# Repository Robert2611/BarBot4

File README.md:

# BarBot4

BarBot4 is a high-end, automated cocktail-mixing machine designed for precision and ease of use. It combines a Raspberry Pi-powered touch interface with modular microcontroller-based hardware to deliver perfectly mixed drinks every time.

## ✨ Features

- **Automated Mixing**: Precise control over ingredient dispensing and sequence.
- **Modular Design**: Support for peripheral modules like mixers, crushers, and straw dispensers.
- **Smart Scale Integration**: Real-time weight tracking for accurate pours.
- **Touchscreen GUI**: Modern, user-friendly interface built with PyQt5.
- **Customizable Recipes**: Easily create and manage your own cocktail database.
- **Wireless Communication**: Bluetooth-based control between the Pi and hardware sub-modules.

## 🛠️ Hardware Requirements

To build a BarBot4, you will need:
- **Main Controller**: Raspberry Pi (Bookworm or Trixie recommended) with a touchscreen.
- **Mainboard**: ESP32-based controller for motor and pump management.
- **Balance Board (Mandatory)**: An Atmega328p-based module for accurate weight sensing.
    - **Sensor**: HX711 Load Cell amplifier for weight measurement.
- **Optional Sub-modules**: AVR (Arduino) based modules for specific functions (e.g., Ice Crusher, Mixer, Straw Dispenser).
- **Firmware**: Pre-compiled binaries for all modules are available in the [GitHub Releases](https://github.com/Robert2611/BarBot4/releases).

## 🚀 Quick Start

### 1. Firmware Installation
For ease of setup, pre-compiled firmware binaries are automatically generated and attached to each [GitHub Release](https://github.com/Robert2611/BarBot4/releases).

1. Download the `firmware.zip` from the latest release.
2. Extract the archive on a Windows PC.
3. Run `flash.bat` and follow the on-screen instructions to flash your Mainboard (ESP32) or sub-modules (Atmega328p).
   - *Note: Flashing scripts for Linux/macOS users can be found in the `/firmware` directory.*

### 2. Pi Software Installation
The easiest way to set up the BarBot software on a fresh Raspberry Pi OS is to use the automated install script:

```bash
curl -sSL https://raw.githubusercontent.com/Robert2611/BarBot4/master/raspberry/install.sh | bash
```

This script handles dependencies, virtual environment setup, and system configuration. **It also configures the application to start automatically on boot**, so there is no need to run it manually after the initial setup.

## 🛠️ Development

If you are developing for BarBot4 or need to run it manually for testing, you can use the following commands:

### Running BarBot Manually
- `barbot`: Start the standard interface.
- `barbot-demo`: Start in demo mode (uses mockup hardware for testing).
- `barbot-with-log`: Start with console logging enabled.

### Local Installation
To install the package in editable mode from the repository:
```bash
cd raspberry
pip install -e .
```

## 📂 Project Structure

The project is organized to separate physical design, electronics, and software:
- `/CAD`: 3D models for the chassis and components.
- `/elektronik`: PCB designs and schematics.
- `/firmware`: Microcontroller source code (C++/PlatformIO).
- `/raspberry`: Main Python application logic and GUI.

For a detailed breakdown of all directories, please refer to [README_STRUCTURE.md](./README_STRUCTURE.md).

## 🤝 Contributing

Contributions are welcome! Whether it's a new recipe, a bug fix, or a feature request, feel free to open an issue or submit a pull request.

## 📜 License
[MIT](https://choosealicense.com/licenses/mit/)

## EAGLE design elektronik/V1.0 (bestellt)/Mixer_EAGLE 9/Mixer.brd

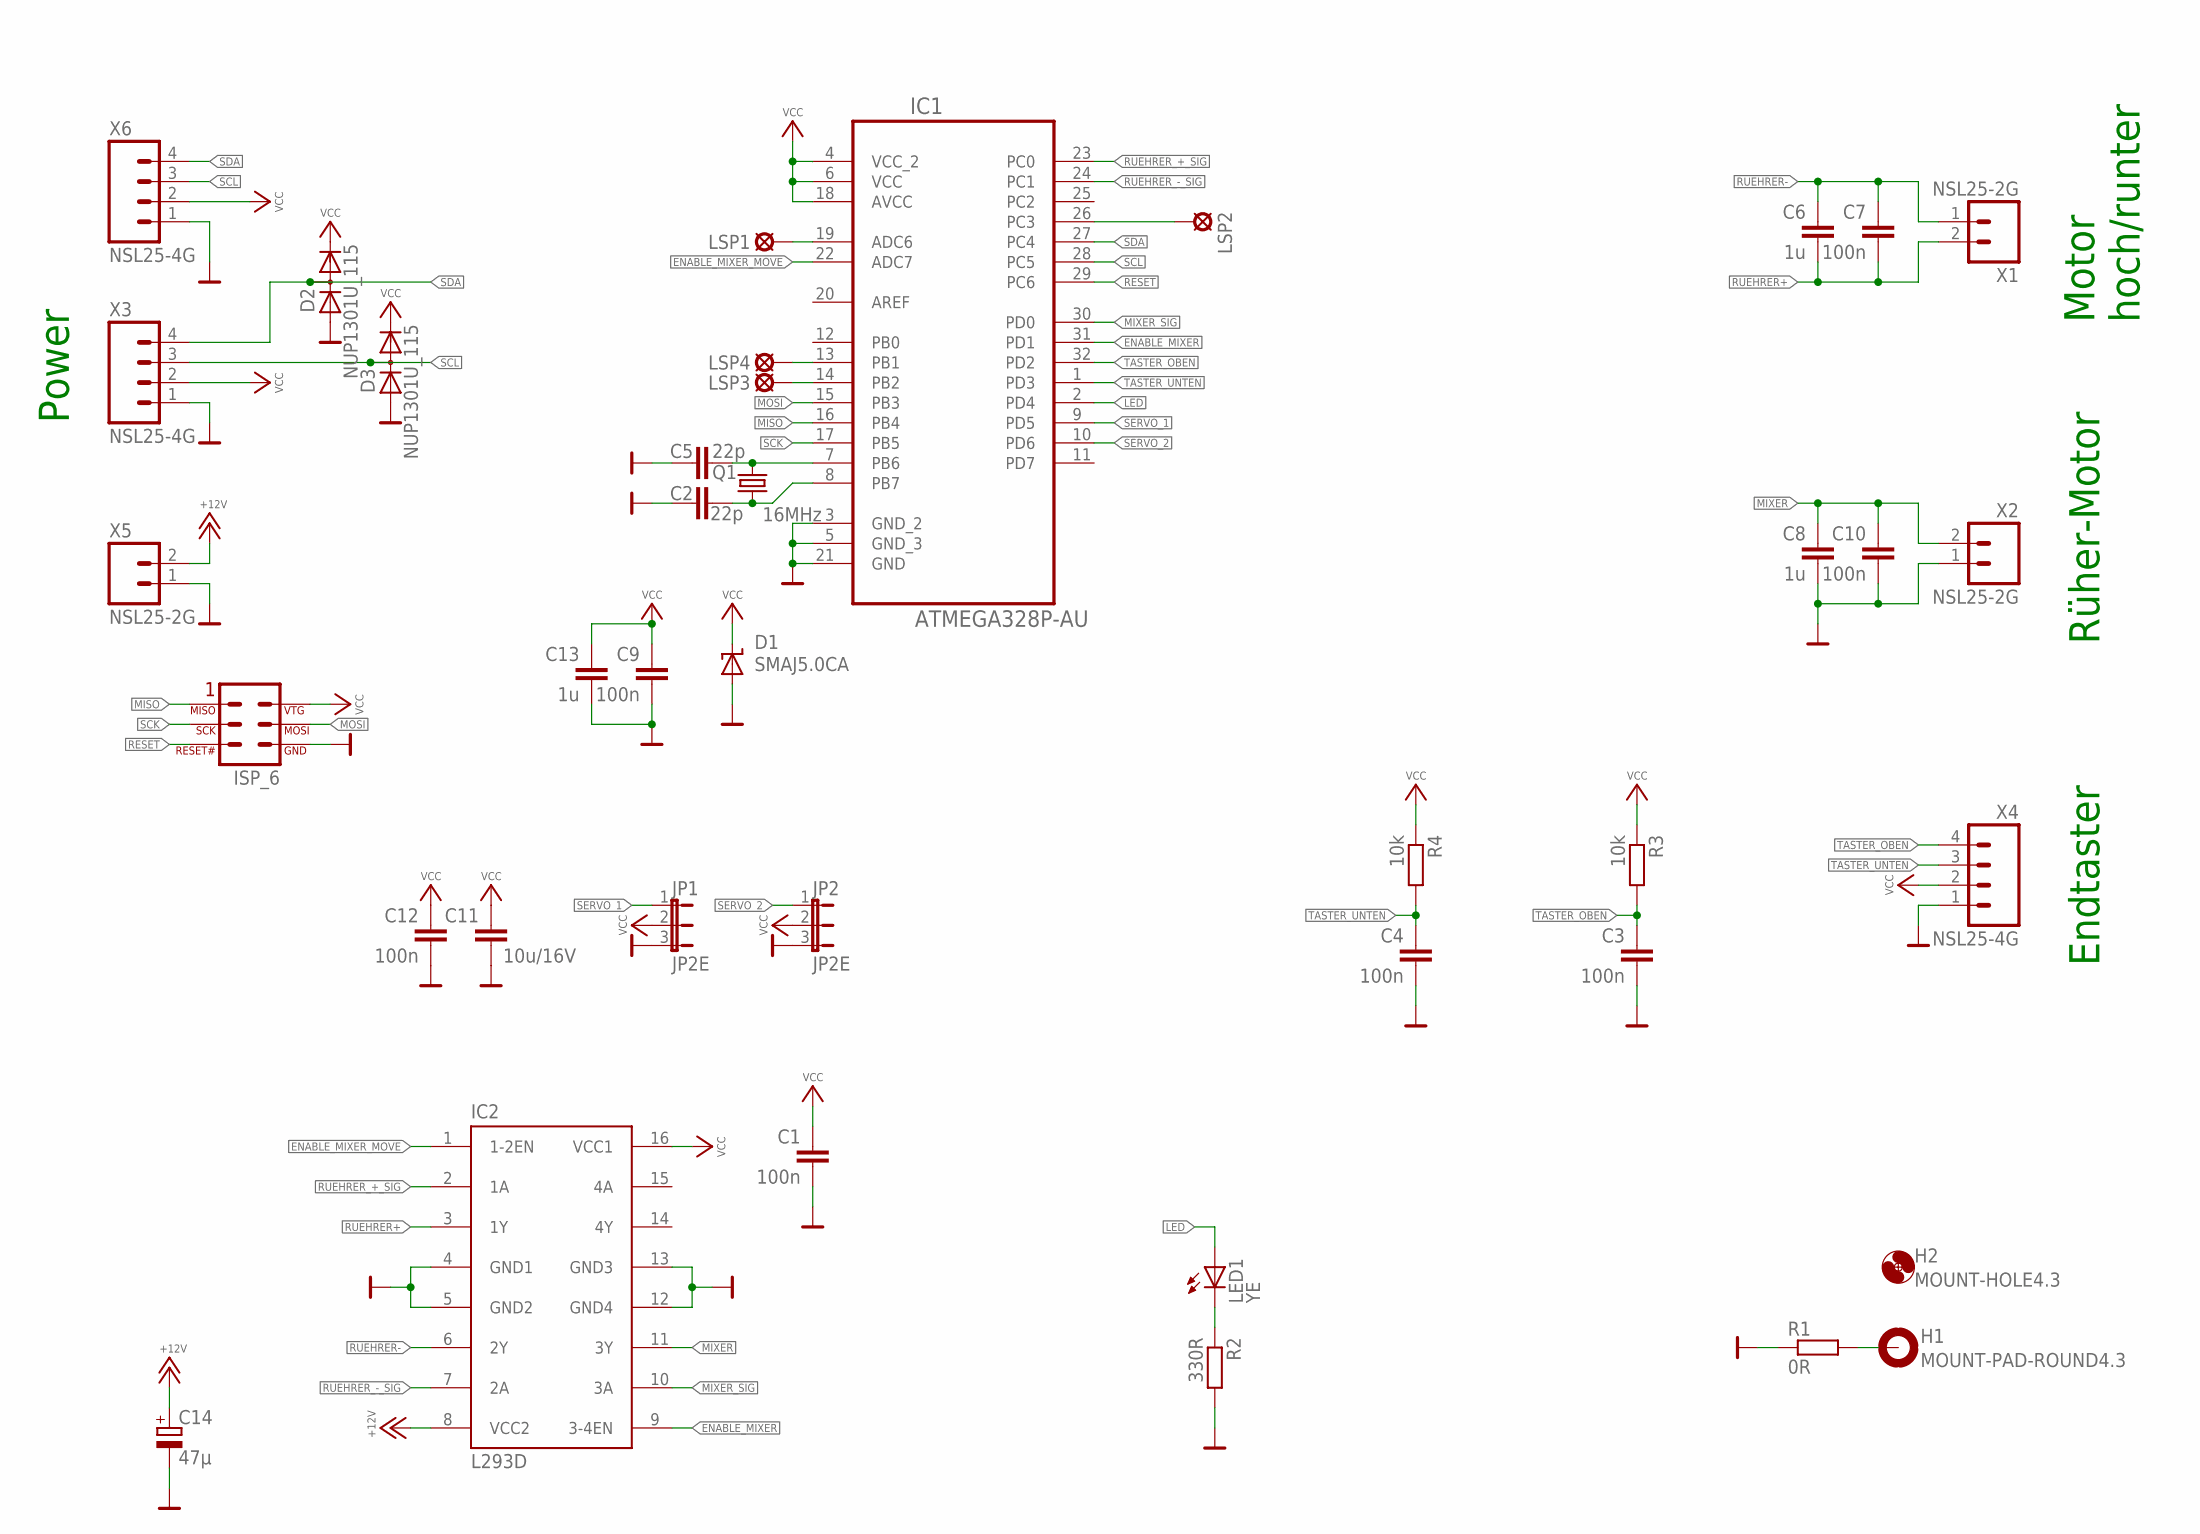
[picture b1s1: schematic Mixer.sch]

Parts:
C1, C3, C4, C7, C9, C10, C12: 100n; 0805CRH
C2, C5: 22p; 0805CRH
C6, C8, C13: 1u; 0805CRH
C11: 10u/16V; 0805CRH
C14: 47µ; 153CLV-0405
D1: SMAJ5.0CA; SMA-DO214AC
D2, D3: NUP1301U_115; SOT323-3
H1: MOUNT-PAD-ROUND4.3; 4,3-PAD
H2: MOUNT-HOLE4.3; 4,3
IC1: ATMEGA328P-AU; QFP80P900X900X120-32N
IC2: L293D; DIL16
JP1, JP2: JP2E; JP2
LED1: YE; CHIPLED_0805
LSP1, LSP2, LSP3, LSP4: LSP06
Q1: 16MHz; HC49UP
R1: 0R; 0805CRH
R2: 330R; 0805CRH
R3, R4: 10k; 0805CRH
SV1: ATMEL_ISP_6; ML6
X1, X2, X5: NSL25-2G
X3, X4, X6: NSL25-4G

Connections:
+12V: C14.+, IC2.8 (VCC2), X5.2
ADC6: IC1.19 (ADC6), LSP1.MP
ENABLE_MIXER: IC1.31 (PD1), IC2.9 (3-4EN)
ENABLE_MIXER_MOVE: IC1.22 (ADC7), IC2.1 (1-2EN)
GND: C1.2, C2.1, C3.2, C4.2, C5.1, C8.2, C9.2, C10.2, C11.2, C12.2, C13.2, C14.-, D1.A, D2.1, D3.1, IC1.3 (GND_2), IC1.5 (GND_3), IC1.21 (GND), IC2.4 (GND1), IC2.5 (GND2), IC2.12 (GND4), IC2.13 (GND3), JP1.3, JP2.3, R1.1, R2.2, SV1.6, X2.1, X3.1, X4.1, X5.1, X6.1
LED: IC1.2 (PD4), LED1.A
MISO: IC1.16 (PB4), SV1.1
MIXER: C8.1, C10.1, IC2.11 (3Y), X2.2
MIXER_SIG: IC1.30 (PD0), IC2.10 (3A)
MOSI: IC1.15 (PB3), SV1.4
unnamed: H1.B4,3, R1.2
unnamed: LED1.C, R2.1
unnamed: IC1.26 (PC3), LSP2.MP
unnamed: C5.2, IC1.7 (PB6), Q1.2
unnamed: C2.2, IC1.8 (PB7), Q1.1
unnamed: IC1.14 (PB2), LSP3.MP
unnamed: IC1.13 (PB1), LSP4.MP
RESET: IC1.29 (PC6), SV1.5
RUEHRER+: C6.2, C7.2, IC2.3 (1Y), X1.2
RUEHRER-: C6.1, C7.1, IC2.6 (2Y), X1.1
RUEHRER_+_SIG: IC1.23 (PC0), IC2.2 (1A)
RUEHRER_-_SIG: IC1.24 (PC1), IC2.7 (2A)
SCK: IC1.17 (PB5), SV1.3
SCL: D3.3, IC1.28 (PC5), X3.3, X6.3
SDA: D2.3, IC1.27 (PC4), X3.4, X6.4
SERVO_1: IC1.9 (PD5), JP1.1
SERVO_2: IC1.10 (PD6), JP2.1
TASTER_OBEN: C3.1, IC1.32 (PD2), R3.2, X4.4
TASTER_UNTEN: C4.1, IC1.1 (PD3), R4.2, X4.3
VCC: C1.1, C9.1, C11.1, C12.1, C13.1, D1.K (C), D2.2, D3.2, IC1.4 (VCC_2), IC1.6 (VCC), IC1.18 (AVCC), IC2.16 (VCC1), JP1.2, JP2.2, R3.1, R4.1, SV1.2, X3.2, X4.2, X6.2

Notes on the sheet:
Power
Rüher-Motor
Endtaster
Motor hoch/runter

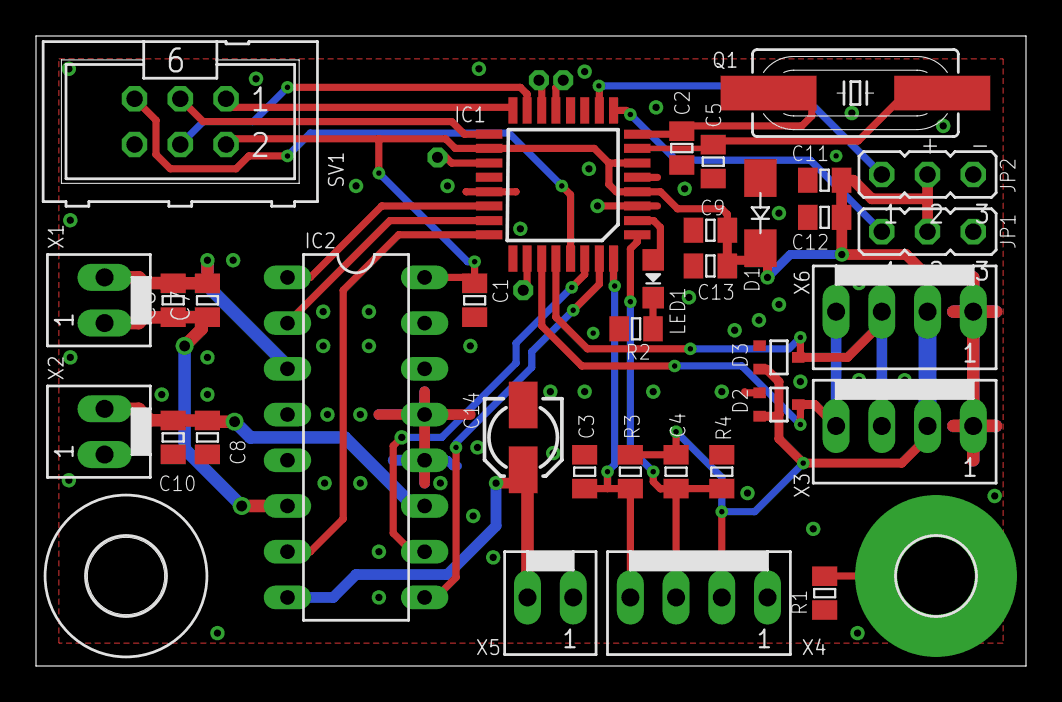
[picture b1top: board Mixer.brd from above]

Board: 2 copper layers, 55.0 x 35.0 mm, 40 parts (0 on the bottom side), 30 nets.

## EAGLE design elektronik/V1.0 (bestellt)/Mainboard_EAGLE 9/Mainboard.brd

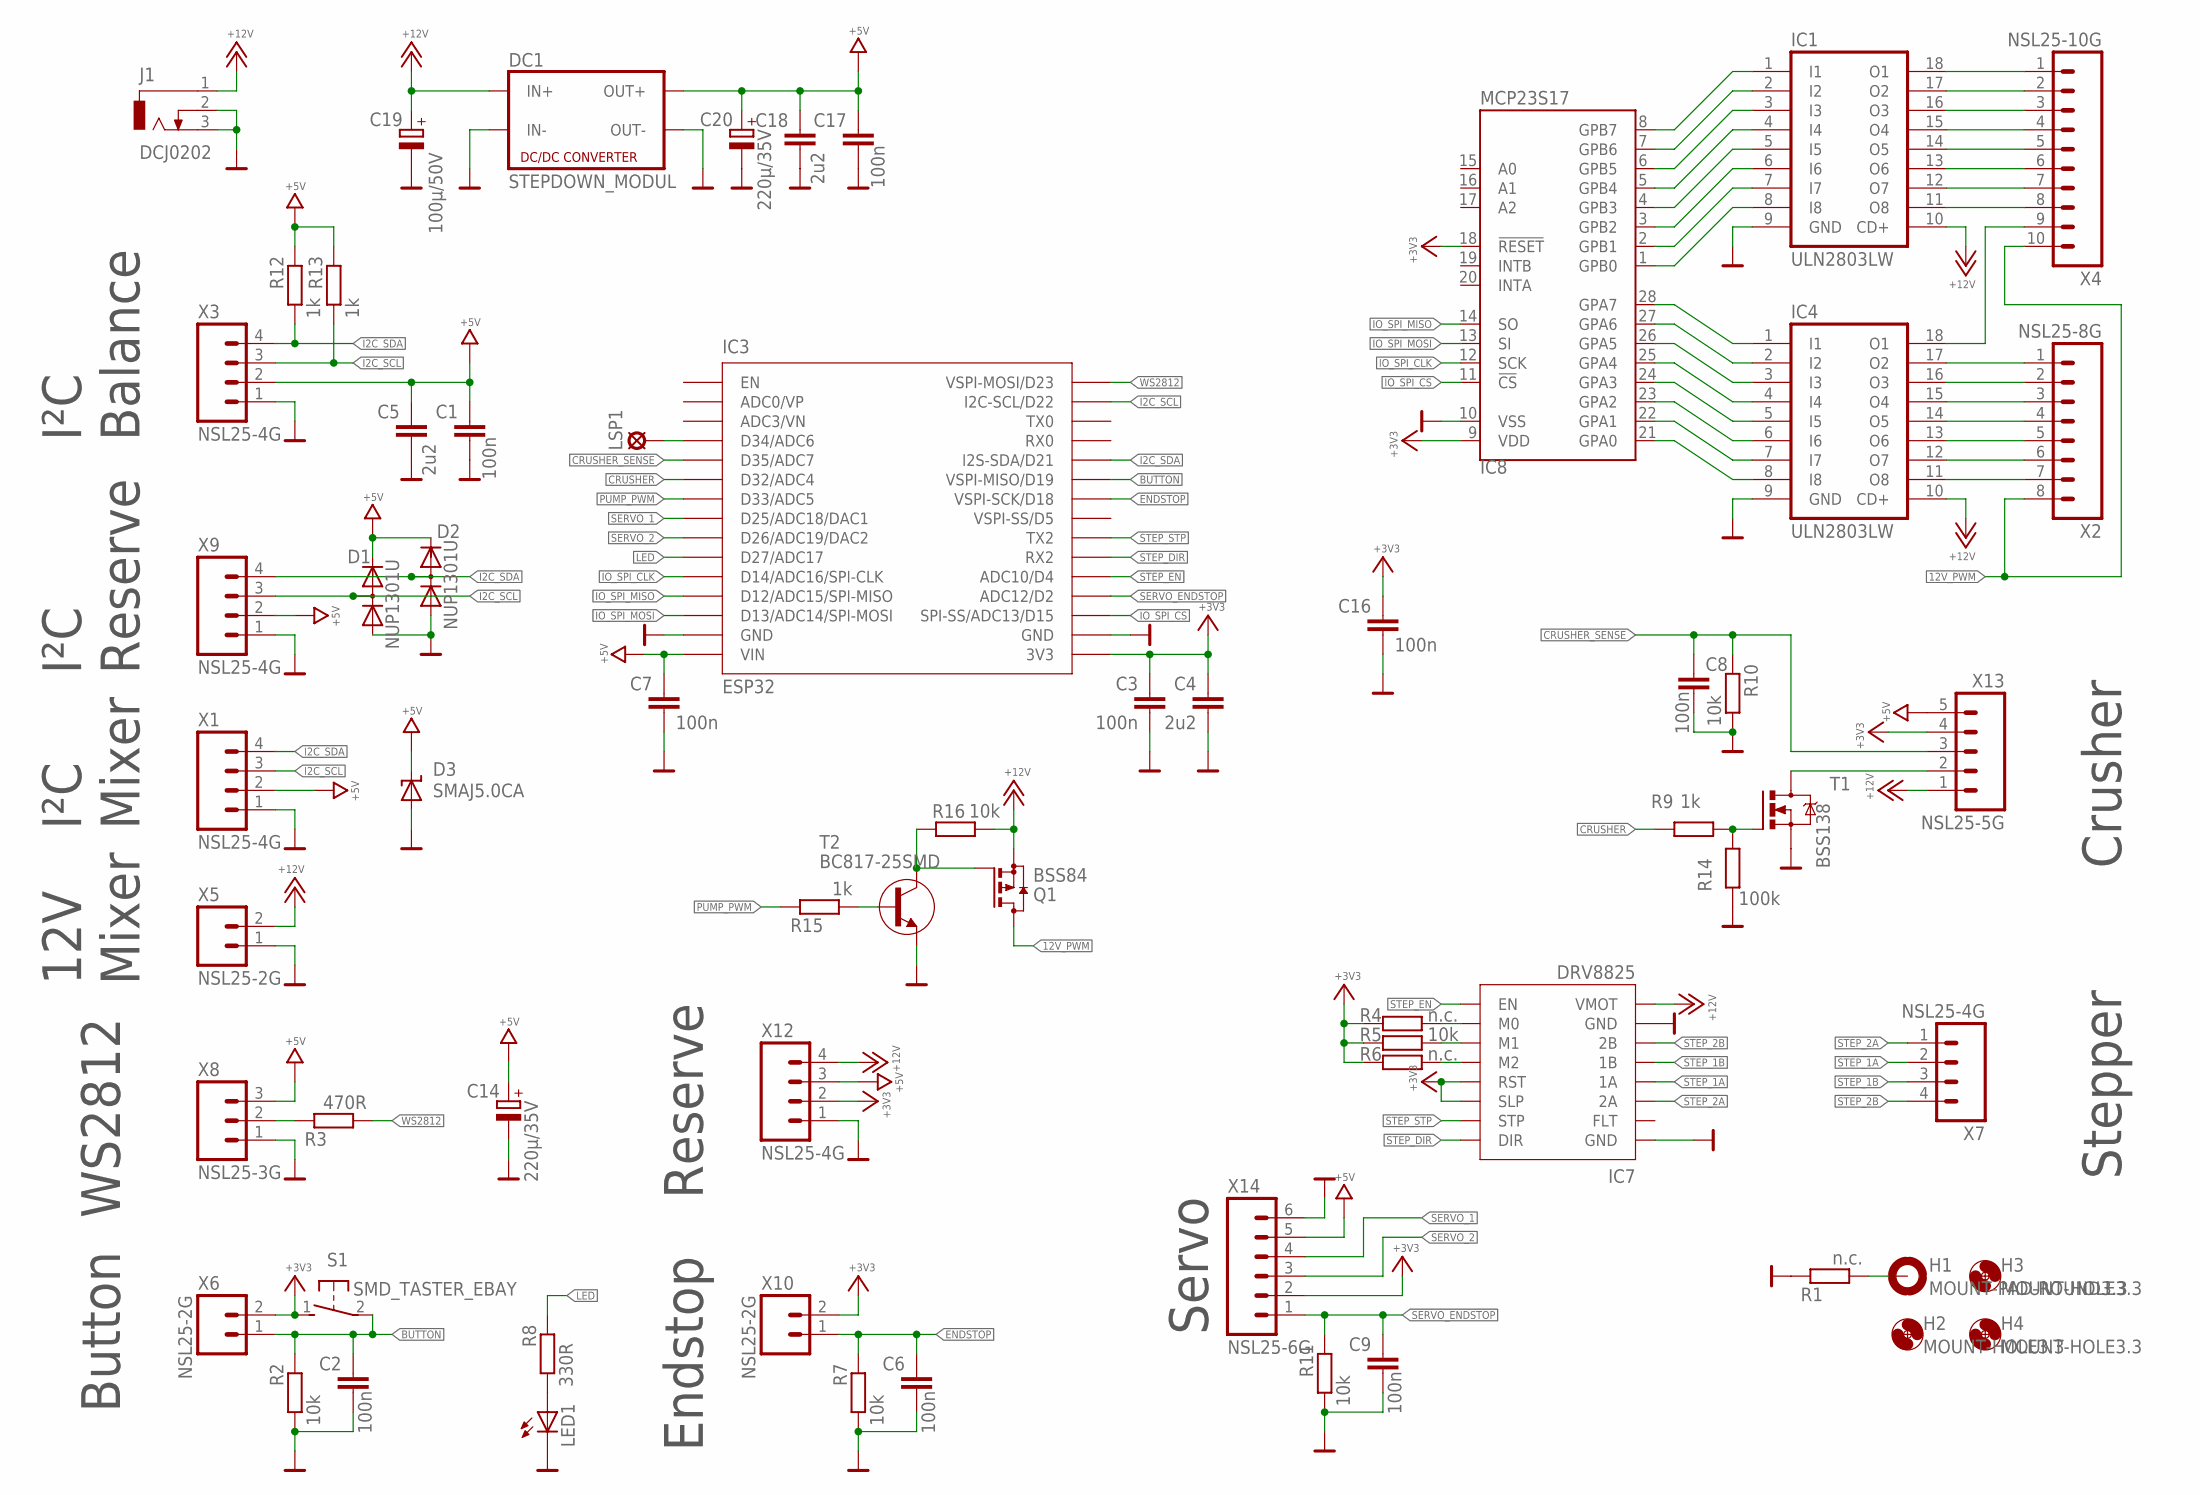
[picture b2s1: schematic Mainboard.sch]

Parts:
C1, C2, C3, C6, C7, C8, C9, C16, C17: 100n; 0805CRH
C4, C5, C18: 2u2; 0805CRH
C14, C20: 220µ/35V; 153CLV-1010
C19: 100µ/50V; 153CLV-1010
D1, D2: NUP1301U; SOT323-3
D3: SMAJ5.0CA; SMA-DO214AC
DC1: STEPDOWN_MODUL
H1: MOUNT-PAD-ROUND3.3; 3,3-PAD
H2, H3, H4: MOUNT-HOLE3.3; 3,3
IC1, IC4: ULN2803LW; SO18W
IC3: ESP32
IC7: DRV8825
IC8: MCP23S17; SOIC-28
J1: DCJ0202
LED1: LEDCHIPLED_0805; CHIPLED_0805
LSP1: LSP06
Q1: BSS84; SOT23
R1, R4, R6: n.c.; 0805CRH
R2, R5, R7, R10, R11, R16: 10k; 0805CRH
R3: 470R; 0805CRH
R8: 330R; 0805CRH
R9, R12, R13, R15: 1k; 0805CRH
R14: 100k; 0805CRH
S1: SMD_TASTER_EBAY; DTSM3XN
T1: BSS138; SOT23
T2: BC817-25SMD; SOT23-BEC
X1, X3, X7, X9, X12: NSL25-4G
X2: NSL25-8G
X4: NSL25-10G
X5, X6, X10: NSL25-2G
X8: NSL25-3G
X13: NSL25-5G
X14: NSL25-6G

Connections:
12V_PWM: Q1.3 (D), X2.8, X4.10
+3V3: C3.1, C4.1, C16.1, IC3.3V3, IC7.RST, IC7.SLP, IC8.9 (VDD), IC8.18 (!RESET!), R4.1, R5.1, R6.1, S1.1 (S), X6.2, X10.2, X12.2, X13.4, X14.2
+5V: C1.1, C5.1, C7.1, C14.+, C17.1, C18.1, C20.+, D1.2, D2.2, D3.K (C), DC1.OUT+, IC3.VIN, R12.1, R13.1, X1.2, X3.2, X8.3, X9.2, X12.3, X13.5, X14.5
+12V: C19.+, DC1.IN+, IC1.10 (CD+), IC4.10 (CD+), IC7.VMOT, J1.1, Q1.2 (S), R16.2, X5.2, X12.4, X13.1
ADC3/VN: IC3.VN (ADC3/VN)
BUTTON: C2.1, IC3.D19 (VSPI-MISO/D19), R2.1, S1.2, X6.1
CRUSHER: IC3.D32 (D32/ADC4), R9.1
CRUSHER_SENSE: C8.1, IC3.D35 (D35/ADC7), R10.1, X13.3
ENDSTOP: C6.1, IC3.D18 (VSPI-SCK/D18), R7.1, X10.1
GND: C1.2, C2.2, C3.2, C4.2, C5.2, C6.2, C7.2, C8.2, C9.2, C14.-, C16.2, C17.2, C18.2, C19.-, C20.-, D1.1, D2.1, D3.A, DC1.IN-, DC1.OUT-, IC1.9 (GND), IC3.GND@1 (GND), IC3.GND@2 (GND), IC4.9 (GND), IC7.GND@1 (GND), IC7.GND@2 (GND), IC8.10 (VSS), J1.2, J1.3, LED1.C, R1.1, R2.2, R7.2, R10.2, R11.2, R14.1, T1.2 (S), T2.E, X1.1, X3.1, X5.1, X8.1, X9.1, X12.1, X14.6
I2C_SCL: D1.3, IC3.D22 (I2C-SCL/D22), R13.2, X1.3, X3.3, X9.3
I2C_SDA: D2.3, IC3.D21 (I2S-SDA/D21), R12.2, X1.4, X3.4, X9.4
IO_SPI_CLK: IC3.D14 (D14/ADC16/SPI-CLK), IC8.12 (SCK)
IO_SPI_CS: IC3.D15 (SPI-SS/ADC13/D15), IC8.11 (!CS!)
IO_SPI_MISO: IC3.D12 (D12/ADC15/SPI-MISO), IC8.14 (SO)
IO_SPI_MOSI: IC3.D13 (D13/ADC14/SPI-MOSI), IC8.13 (SI)
LED: IC3.D27 (D27/ADC17), R8.1
unnamed: LED1.A, R8.2
unnamed: T1.3 (D), X13.2
unnamed: R9.2, R14.2, T1.1 (G)
unnamed: Q1.1 (G), R16.1, T2.C
unnamed: R15.2, T2.B
unnamed: IC3.D34 (D34/ADC6), LSP1.MP
unnamed: R3.1, X8.2
unnamed: H1.B3,3, R1.2
unnamed: IC4.8 (I8), IC8.21 (GPA0)
unnamed: IC4.7 (I7), IC8.22 (GPA1)
unnamed: IC4.6 (I6), IC8.23 (GPA2)
unnamed: IC4.5 (I5), IC8.24 (GPA3)
unnamed: IC4.4 (I4), IC8.25 (GPA4)
unnamed: IC4.3 (I3), IC8.26 (GPA5)
unnamed: IC4.2 (I2), IC8.27 (GPA6)
unnamed: IC1.18 (O1), X4.1
unnamed: IC1.17 (O2), X4.2
unnamed: IC1.16 (O3), X4.3
unnamed: IC1.15 (O4), X4.4
unnamed: IC1.14 (O5), X4.5
unnamed: IC1.13 (O6), X4.6
unnamed: IC1.12 (O7), X4.7
unnamed: IC1.11 (O8), X4.8
unnamed: IC4.18 (O1), X4.9
unnamed: IC4.17 (O2), X2.1
unnamed: IC4.16 (O3), X2.2
unnamed: IC4.15 (O4), X2.3
unnamed: IC4.14 (O5), X2.4
unnamed: IC4.13 (O6), X2.5
unnamed: IC4.12 (O7), X2.6
unnamed: IC4.11 (O8), X2.7
unnamed: IC4.1 (I1), IC8.28 (GPA7)
unnamed: IC1.8 (I8), IC8.1 (GPB0)
unnamed: IC7.M0, R4.2
unnamed: IC7.M1, R5.2
unnamed: IC7.M2, R6.2
unnamed: IC1.7 (I7), IC8.2 (GPB1)
unnamed: IC1.6 (I6), IC8.3 (GPB2)
unnamed: IC1.5 (I5), IC8.4 (GPB3)
unnamed: IC1.4 (I4), IC8.5 (GPB4)
unnamed: IC1.3 (I3), IC8.6 (GPB5)
unnamed: IC1.2 (I2), IC8.7 (GPB6)
unnamed: IC1.1 (I1), IC8.8 (GPB7)
PUMP_PWM: IC3.D33 (D33/ADC5), R15.1
SERVO_1: IC3.D25 (D25/ADC18/DAC1), X14.4
SERVO_2: IC3.D26 (D26/ADC19/DAC2), X14.3
SERVO_ENDSTOP: C9.1, IC3.D2 (ADC12/D2), R11.1, X14.1
STEP_1A: IC7.1A, X7.2
STEP_1B: IC7.1B, X7.3
STEP_2A: IC7.2A, X7.1
STEP_2B: IC7.2B, X7.4
STEP_DIR: IC3.RX2, IC7.DIR
STEP_EN: IC3.D4 (ADC10/D4), IC7.EN
STEP_STP: IC3.TX2, IC7.STP
WS2812: IC3.D23 (VSPI-MOSI/D23), R3.2

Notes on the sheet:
I²C Balance
I²C Mixer
12V Mixer
WS2812
I²C Reserve
Button
Endstop
Reserve
Stepper
Crusher
Servo

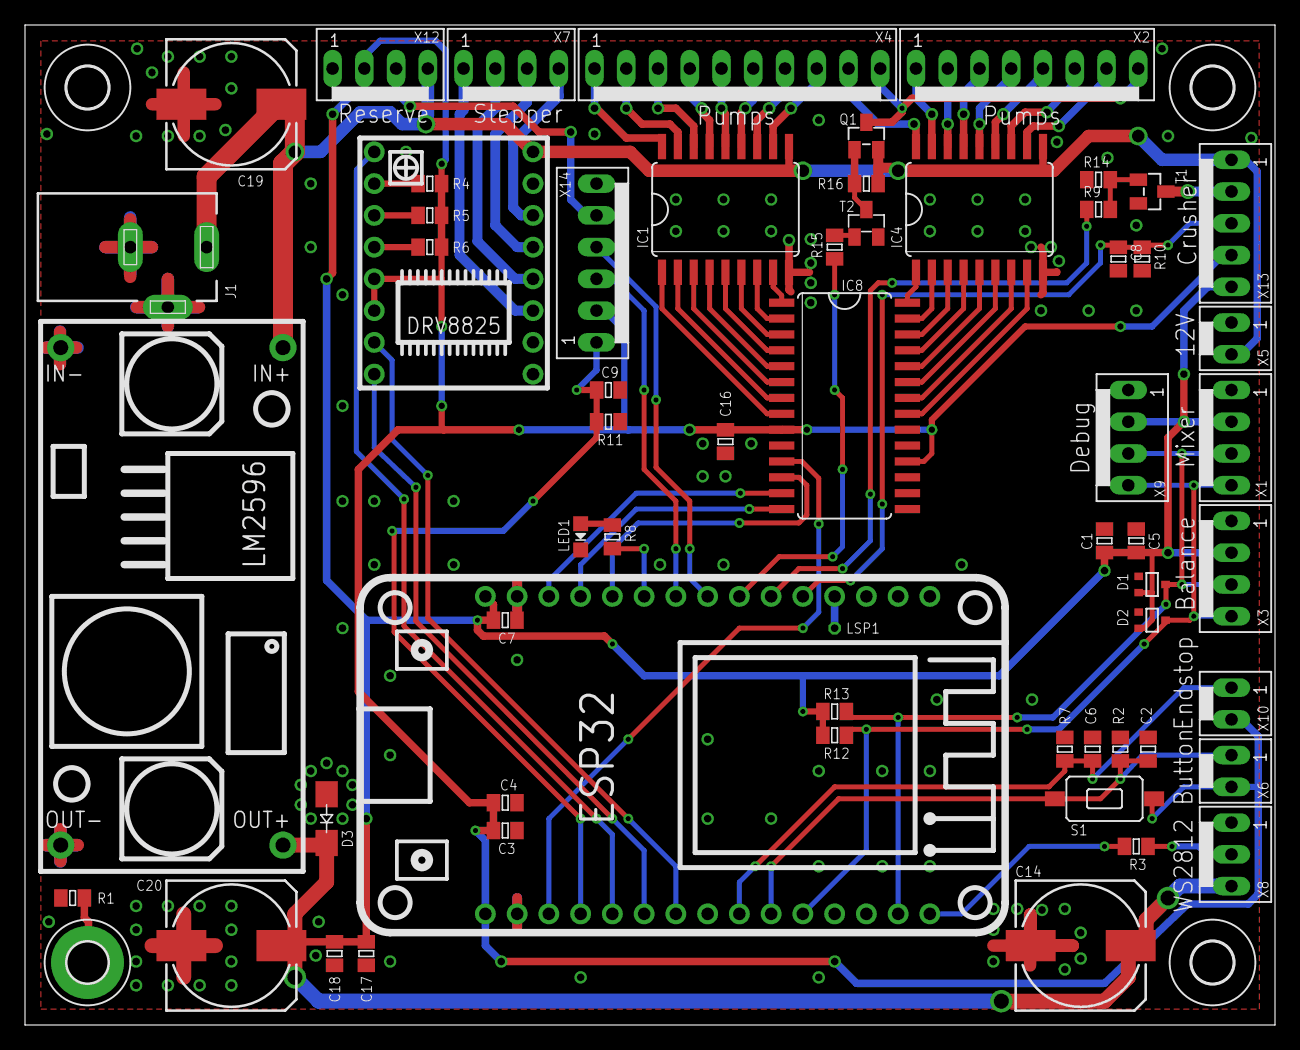
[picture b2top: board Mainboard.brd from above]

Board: 2 copper layers, 100.0 x 80.0 mm, 64 parts (0 on the bottom side), 71 nets.

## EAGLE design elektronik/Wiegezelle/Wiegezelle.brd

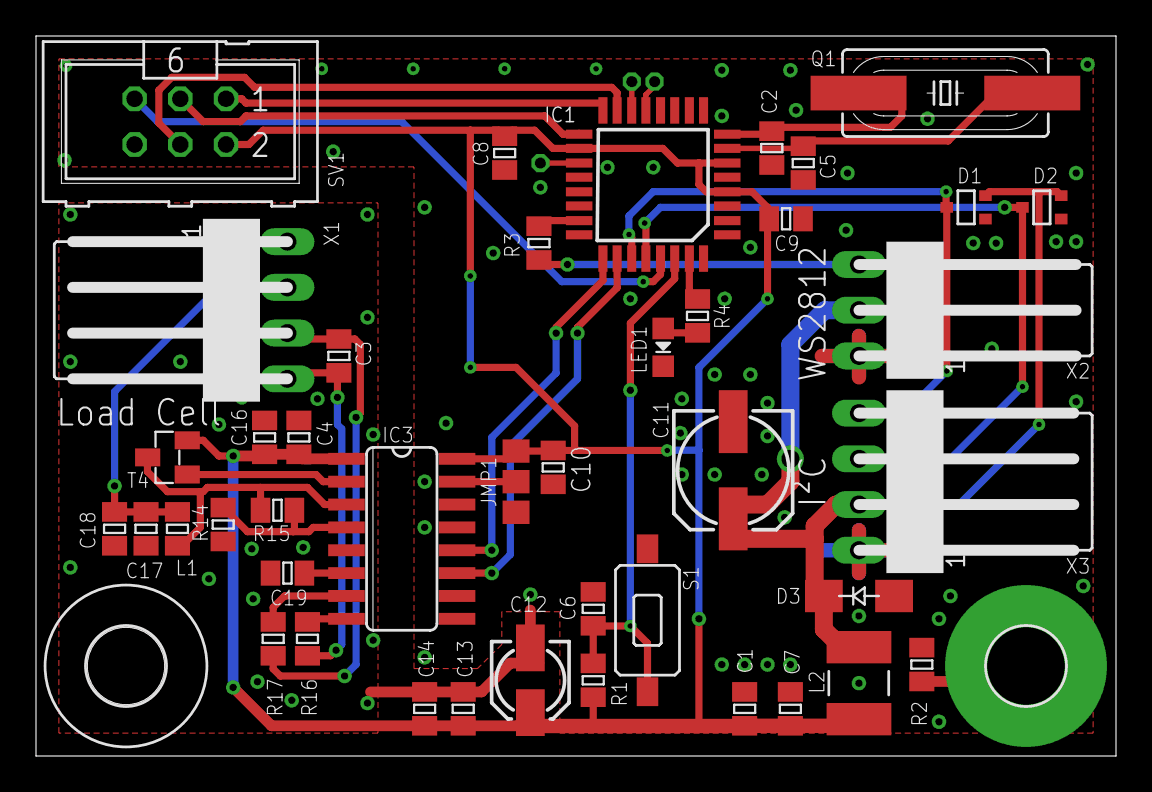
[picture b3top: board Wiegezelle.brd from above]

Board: 2 copper layers, 60.0 x 40.0 mm, 47 parts (0 on the bottom side), 33 nets.

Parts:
C1: 1n; 0805CRH
C2, C5: 22p; 0805CRH
C3, C6, C7, C8, C9, C10, C14, C16, C17, C19: 100n; 0805CRH
C4: 1u; 0805CRH
C11: 100u; 153CLV-0605
C12: 47u; 153CLV-0405
C13: 2u2; 0805CRH
C18: 10u; 0805CRH
D1, D2: NUP1301U_115; SOT323-3
D3: SMAJ5.0CA; SMA-DO214AC
H1: MOUNT-PAD-ROUND4.3; 4,3-PAD
H2: MOUNT-HOLE4.3; 4,3
IC1: ATMEGA328P-AU; QFP80P900X900X120-32N
IC3: HX711; SO16
JMP1: 0R-JUMPA; A0R-JMP
L1: 3u3; 0805CRH
L2: 22u; L4532P
LED1: YE; CHIPLED_0805
LSP1, LSP2, LSP3: LSP06
Q1: 16MHz; HC49UP
R1: 10k; 0805CRH
R2: 0R; 0805CRH
R3: 470R; 0805CRH
R4: 220R; 0805CRH
R14: 1k; 0805CRH
R15: 2k2; 0805CRH
R16, R17: 100R; 0805CRH
S1: SMD_TASTER_EBAY; DTSM3XN
SV1: ATMEL_ISP_6; ML6
T4: BC807-16SMD; SOT23-BEC
X1, X3: NSL25-4W
X2: NSL25-3W

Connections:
AGND: C4.2, C12.-, C13.2, C14.2, C16.2, C17.2, C18.2, C19.2, IC3.5, R14.2, X1.1
GND: C1.2, C2.1, C5.1, C6.2, C7.2, C8.2, C9.2, C10.2, C11.-, D1.1, D2.1, D3.A, IC1.3, IC1.5, IC1.21, IC3.14, JMP1.3, LED1.C, R2.1, S1.2, SV1.6, X2.1, X3.1
HX711_DT: IC1.25, IC3.12
HX711_SCK: IC1.26, IC3.11
INA+: IC3.8, R16.1
INA-: IC3.7, R17.1
LED: IC1.31, R4.1
LED_DATA: IC1.23, R3.1
MISO: IC1.16, SV1.1
MOSI: IC1.15, SV1.4
unnamed: H1.B4,3, R2.2
unnamed: LED1.A, R4.2
unnamed: R3.2, X2.3
unnamed: C5.2, IC1.7, Q1.2
unnamed: C2.2, IC1.8, Q1.1
unnamed: IC1.19, LSP1.MP
unnamed: IC1.13, LSP2.MP
unnamed: IC1.14, LSP3.MP
unnamed: IC3.15, JMP1.2
unnamed: C19.1, IC3.6
unnamed: IC3.2, T4.B
unnamed: IC3.4, R14.1, R15.2
unnamed: C3.1, R16.2, X1.4
unnamed: C3.2, R17.2, X1.3
RESET: IC1.29, SV1.5
SCK: IC1.17, SV1.3
SCL: D2.3, IC1.28, X3.3
SDA: D1.3, IC1.27, X3.4
TASTER: C6.1, IC1.30, R1.2, S1.1
VAVDD: C17.1, C18.1, L1.2, X1.2
VAVDD_1: IC3.3, L1.1, R15.1, T4.C
VCC: C1.1, C4.1, C7.1, C8.1, C9.1, C10.1, C12.+, C13.1, C14.1, C16.1, IC1.4, IC1.6, IC1.18, IC3.1, IC3.16, JMP1.1, L2.1, R1.1, SV1.2, T4.E
VCC_INPUT: C11.+, D1.2, D2.2, D3.K, L2.2, X2.2, X3.2

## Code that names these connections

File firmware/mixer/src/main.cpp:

#include <Arduino.h>
#include "Wire.h"
#include "Shared.h"
#include "WireProtocol.h"

#define PIN_EN A7            //ADC7
#define PIN_MOTOR_1 A0       //PC0
#define PIN_MOTOR_2 A1       //PC1
#define PIN_ENDSTOP_TOP 2    //PD2
#define PIN_ENDSTOP_BOTTOM 3 //PD3
#define PIN_MIXER_EN 1       //PD1
#define PIN_MIXER 0          //PD0
#define PIN_LED 4            //PD4
#define PIN_BUTTON 10        //PB2
//not used but still on the PCB
#define PIN_SERVO_1 5 //PD5
#define PIN_SREVO_2 6 //PD6

#define MIXING_MIN_TIME 500      // avoid very short...
#define MIXING_MAX_TIME 5000     // ... and very long mixes
#define MIXING_MOVE_TIMEOUT 3000 //no success if move takes too long
#define MIXING_DEFAULT_TIME 2000 //will be used if no time is set

byte i2c_command = 0xFF;

bool do_mixing;
bool error;
long mixing_time = 1000;

void startMixing(long _mixing_time)
{
  if (do_mixing)
    return;
  error = false;
  do_mixing = true;
  mixing_time = constrain(_mixing_time, MIXING_MIN_TIME, MIXING_MAX_TIME);
  digitalWrite(PIN_LED, HIGH);
}

void stopMixing(bool _error)
{
  error = _error;
  do_mixing = false;
  digitalWrite(PIN_LED, LOW);
}

void handleSetters(int parameters_count)
{
#ifdef SERIAL_DEBUG
  Serial.print("SET");
  Serial.println(i2c_command);
#endif
  switch (i2c_command)
  {
  case MIXER_CMD_START_MIXING:
    if (parameters_count == 0)
    {
      startMixing(MIXING_DEFAULT_TIME);
    }
    else if (parameters_count == 1)
    {
      byte time_in_seconds = Wire.read();
      startMixing((unsigned long)time_in_seconds * 1000);
    }
    break;
  }
}

void handleGetters()
{
#ifdef SERIAL_DEBUG
  Serial.print("GET");
  Serial.println(i2c_command);
#endif
  switch (i2c_command)
  {
  case WIREPROTOCOL_CMD_PING:
    Wire.write(MIXER_BOARD_ADDRESS);
    break;
  case MIXER_CMD_GET_IS_MIXING:
    Wire.write(do_mixing);
    break;

  case MIXER_CMD_GET_SUCCESSFUL:
    Wire.write(!error);
    break;

  //no command byte set or unknown command
  case 0xFF:
  default:
#ifdef SERIAL_DEBUG
    Serial.println("Wrong request");
#endif
    Wire.write(0);
    i2c_command = 0xFF;
    break;
  }
}

void recieved(int count)
{
  //continue only if command byte was set
  if (count < 1)
    return;
  //save the command byte
  i2c_command = Wire.read();
  //handle messages that are only setters
  handleSetters(count - 1);
}

void initWire()
{
  //start i2c communication
  Wire.begin(MIXER_BOARD_ADDRESS);
  //disable pullups for i2c
  digitalWrite(SCL, LOW);
  digitalWrite(SDA, LOW);
  Wire.onReceive(recieved);
  Wire.onRequest(handleGetters);
  WireProtocol::blinkAddress(MIXER_BOARD_ADDRESS, PIN_LED);
}

void setup()
{
#ifdef SERIAL_DEBUG
  Serial.begin(115200);
#endif
  pinMode(PIN_LED, OUTPUT);
  pinMode(PIN_EN, OUTPUT);
  pinMode(PIN_MOTOR_1, OUTPUT);
  pinMode(PIN_MOTOR_2, OUTPUT);
  pinMode(PIN_ENDSTOP_TOP, INPUT);
  pinMode(PIN_ENDSTOP_BOTTOM, INPUT);
  pinMode(PIN_MIXER_EN, OUTPUT);
  pinMode(PIN_MIXER, OUTPUT);
  pinMode(PIN_BUTTON, INPUT_PULLUP);
  //disable the driver
  digitalWrite(PIN_MOTOR_1, HIGH);
  digitalWrite(PIN_MOTOR_2, HIGH);
  digitalWrite(PIN_EN, HIGH);
  digitalWrite(PIN_MIXER_EN, LOW);
  initWire();
#ifdef SERIAL_DEBUG
  Serial.println("Mixer board initialised");
#endif
}

bool isAtTop()
{
  return !digitalRead(PIN_ENDSTOP_TOP) && !digitalRead(PIN_ENDSTOP_TOP);
}

bool isAtBottom()
{
  return !digitalRead(PIN_ENDSTOP_BOTTOM) && !digitalRead(PIN_ENDSTOP_BOTTOM);
}

void startMotor(bool up)
{
  digitalWrite(PIN_MOTOR_1, up ? HIGH : LOW);
  digitalWrite(PIN_MOTOR_2, up ? LOW : HIGH);
}

void stopMotor()
{
  digitalWrite(PIN_MOTOR_1, HIGH);
  digitalWrite(PIN_MOTOR_2, HIGH);
}

void toggleMixer(bool on)
{
  digitalWrite(PIN_MIXER, HIGH);
  digitalWrite(PIN_MIXER_EN, on ? HIGH : LOW);
}

void loop()
{
  //wait for i2c command or button press, stay in top position
  while (!do_mixing && digitalRead(PIN_BUTTON) == HIGH)
  {
    if (!isAtTop())
      startMotor(true);
    else
      stopMotor();
    delay(1);
  }
  if (!do_mixing)
    startMixing(MIXING_DEFAULT_TIME);

  //move down
  startMotor(false);
  unsigned long before_move = millis();
  while (!isAtBottom())
  {
    if (millis() > before_move + MIXING_MOVE_TIMEOUT)
    {
      //TIMEOUT,
      stopMixing(true);
      return;
    }
    delay(1);
  }

  stopMotor();

  //mix
  toggleMixer(true);
  delay(mixing_time);
  toggleMixer(false);

  //move up
  startMotor(true);

  before_move = millis();
  while (!isAtTop())
  {
    if (millis() > before_move + MIXING_MOVE_TIMEOUT)
    {
      //TIMEOUT,
      stopMixing(true);
      return;
    }
    delay(1);
  }

  stopMixing(false);
}

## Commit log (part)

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2019-04-08 Definitions for ATMEGA8 added
2019-04-09 Protocol upgraded with state machine support
2019-04-10 Revert "Protocol upgraded with state machine support_2"
    This reverts commit b019bc0e1c483c602313dabbec1935119e7cba01.
2019-04-10 Switched to FastLED, LED Animations added
2019-04-14 Statistics added tp GUI
2019-04-14 Order icon changed to bigger one
2019-04-17 mozilla and webkit settings removed from css
2019-04-24 overlayer messages moved to templates
2019-04-24 Instructions added to recipes
2019-04-27 RGB renamed to RGB_t
2019-04-27 Platform movement implemented
2019-05-03 Removing of recipes added to admin area
2019-05-22 I2C communication moved to class WireProtocol
2019-05-22 Automated Link added
2019-05-24 Communication between server and arduino updated
2019-05-28 Balance board changed to Neopixel
2019-05-30 I2C Troubleshooting
2019-05-31 Handling of empty ingredient added
2019-07-24 Mixer firmware added
2019-08-28 Qt MainWindow added
2019-08-29 View classes created
2019-08-31 Structure improved, packages created
2019-09-05 Admin pages added
2019-09-06 BusyView and cleaning added
2019-09-09 Icons moved to asset folder
2019-09-09 Touch keyboard created
2019-09-14 Cleaned up the setup process
2019-09-14 QtChart BarChart replaced with own BarChart
2019-09-15 Logging enabled, prints removed
2019-09-26 MCP23X17 library added
2019-09-26 Gui bugs on windows solved
2019-11-01 - MCP23S17 as pump driver - Display support improved
2019-11-11 Pump index based lighting added
2019-11-12 Straw board added
2019-11-17 New milled straw dispenser board
2019-11-17 General improvements of barbot and gui
2019-11-27 cmdline.txt removed from setup
2019-11-28 Admin mode ad doubleclick of header
2019-11-28 Detection of OS fixed
2019-11-29 Gui exit bug fixed
2019-11-29 Bugfix: in_waiting crashed when hardware unplugged
2019-12-03 Setup folder merged to main folder
2019-12-04 Bugfix: Abort of cocktail after stirring
2019-12-05 Check glas before draft added, display removed
2019-12-07 Recipe filtering added
2019-12-07 Classes for Recipe and RecipeItem created
2019-12-08 Maximum cocktail size added
2019-12-12 Background added to GUI, old style removed
2019-12-20 Mixer board reworked, it is now independent
2019-12-23 Cleaning with adapter added
2019-12-27 Glas indicators added, database format improved
2019-12-30 New positions with new hardware
2019-12-30 Optimizations for raspberry
2019-12-30 Bugfix
2020-01-03 Bugfixes and gui optimizations from newyears
2020-01-10 Automated finding of bluetooth device added
2020-03-31 Build workflow for firmwares added
2020-03-31 debug workflow
2020-03-31 Mainboard and balance folders made lower case
2020-03-31 Bugfix workflow
2020-04-01 Crusher functionality added to mainboard
2020-04-01 Global mixing time now defined in config
2020-04-03 Worklfow now only for firmware folder pushes
2020-05-03 CAD: Version 0.0
2020-05-06 PCBs V1.0
2020-05-07 CAD:Dichtung entfernt,Teile angepasst
2020-05-14 BOM:Artikel hinzugefügt
2020-06-05 BOM: Filamentbedarf für Druckteile hinzugefügt
2020-07-31 Teile hinzugefügt
2020-08-08 Python Debugger description for VSCode added
2020-08-12 BOM: Rollenschalter von Schlitten nach Rahmen
2020-10-15 Durchmesser angepasst
2020-10-15 Teil hinzugefügt
2020-10-16 Do not try to find barbot MAC-address on windows
2020-10-17 Balance calibration in config renamed
2020-10-23 Bugfix for new Raspberry Pi OS
2020-10-25 Position of pumps and mixer adjusted
2020-10-25 Header click for admin window improved for touch
2020-10-28 Balance folder with wrong capital name removed
2020-11-01 Search for BT device moved to state machine
2020-11-01 Class created for Config of BarBot
2021-03-18 New board for crusher
2021-03-21 Ice crushing added to single ingredient page
2021-04-02 Ice, straw and stirring added as icon buttons
2021-04-03 Settings view added
2021-04-03 Electronics folder resturctured
2021-04-10 Error handling improved, bugs removed
2021-04-11 Logs moved to separate folder
2021-04-18 Crusher errors implemented
2021-07-25 Bugfix: Admin crashed with balance unavailable
2021-07-25 Weight update in admin stabalized
2021-07-31 Check for connected boards at startup
2021-07-31 Assets cleaned
2021-08-08 Different timeout for ice crushing
2021-08-15 Barbot tools added for debugging
2021-08-15 Minor fix in mainboard firmware
2021-08-15 BarBotTools added to debug config
2021-08-16 Blocking set and get command implemented for I2C
2021-08-20 CAD: Crusher hinzugefügt
2021-08-22 Rework of classes into modules started
2021-08-23 Demo without running without DB
2021-08-23 dbexport.py added to export recipes to yaml
2021-08-24 Saving and loading of recipes completed
2021-08-25 Statistics work without db
2021-08-26 Python imports cleaned
2021-08-26 Id removed from dbexport
2021-08-26 Bugfix: Incomplete renaming of bot to statemachine
2021-08-26 Bugfix: Balance calibration
2021-08-26 Bugfix: Async set for balance calibration
2021-08-28 fixed recipes introduced
2021-08-30 python requirements updated
2021-08-31 Ingredients added
2021-09-05 Crusher with arduino hardware
2021-09-05 Bugfix: Recipe was changed when ingredient was empty
2021-09-05 Multiple bugfixes
2021-09-05 Bugfix for splashscreen
2021-09-12 Ability to abort commands added to mainboard
2021-09-13 Instruction split into pre and post instruction
2021-09-13 Order recipe view added to ask for ice and straw
2021-09-13 Offset vertical touch position by 1%
2021-09-16 AVRDude and script for flashing added
2022-06-25 Files for raspberry pi moved to separater folder
2022-06-26 Gin added as an ingredient
2022-06-27 Bugfix: Test line removed
2022-07-02 Raspberry pi update script added
2022-07-02 Firmware flashing for mainboard
2022-08-05 Bugfix: Crusher hardware pins were wrong
2022-08-05 Bugfix: Flash script not working in some folders
2022-09-11 Bugfix: Crusher UART interfered with safety switch
2023-08-11 Readme updated
2023-08-11 Dump of version number at release
2023-09-11 Fimware binaries removed from repository
2023-09-11 flash.bat now supports esp32 mainboard
2023-09-24 Mixer board layout exported from Eagle
2023-10-01 Sugar board added to GUI
2023-10-03 LED simulator for Neopixels added
2023-10-06 Bugfixes for sugar dispenser
2023-10-06 Numpad for spinboxes in admin view added
2023-10-23 Timeout for bluetooth communication added
2023-10-24 Bugfix: Numpad did not always open in settings window
2023-11-18 Fixed problem when STATUS was received instead of ACK
2023-11-18 Logging improved
2023-11-18 Fixed display of amount. Wait longer after cocktail is done
2023-11-19 Display of version added to admin view
2023-11-19 Proper handling of SIGINT
2023-11-21 Communication to controller reworked
2023-11-22 Logging added for low level communication errors
2023-11-22 Logging for read_line added
2023-11-28 Fixed copy of recipes to data folder
2023-11-28 Added density of ingredients
2023-11-30 Added terminal output to debug setup
2023-12-09 barbot refactored
2023-12-09 Gui rework started
2023-12-11 gui classes restructured to avoid circular imports
2023-12-14 Barbot is running again
2023-12-18 Update script
2023-12-20 Mixing options and recipe filters
2023-12-20 Gui circular imports removed
2023-12-20 First unittest added
2023-12-22 Unittest for recipes added
2023-12-23 Fixes...
2023-12-30 Mainboard: Fimware versioning added
2023-12-30 Read out firmware version when connecting to barbot
2024-01-09 Mainboard communication mockup improved
2024-01-11 Views refactored
2024-01-17 Tests added to VS code config
2024-01-19 Faster response in idle state
2024-01-20 Magic numbers for LED modes removed
2024-01-20 Readded move to 0
2024-04-05 Unittests for mainboard communication extended
2024-04-07 Gui test improved
2024-04-07 New ingredients added
2024-04-07 Alternative set of cocktails added
2024-04-11 Waiting for user input is no longer blocking communication
2024-04-11 Bugfix in statistics view
2024-04-11 touch_rotate.sh and update.sh made executable
2024-05-17 Recipes updated after test mixing
2024-06-14 Fix: Missing buttons in order screen
2024-06-14 Fixed wrong typehints
2024-06-24 Pylint used to check for typing errors
2025-10-03 Switched to pyproject.toml
2025-10-04 Install and update process reworked
2025-10-04 Fixes in setup
2026-01-02 Split python files in logic folder
2026-01-03 Intermediate state of new statemachine structure
2026-01-08 Unittests work again
2026-01-12 Remove unused cleaning state
2026-01-16 Fix reconnect, add unittests
2026-01-31 feat: Refactor GUI views to be independent of the main window and use signals for communication.
2026-01-31 Remove unused `_state_changed` attribute and a debug log message for no state transitions.
2026-01-31 refactor: modularize GUI views into dedicated user and admin subdirectories.
2026-02-06 test: Add unit tests for barbot states, party, and recipe collection logic.
2026-02-06 refactor: modularize communication layer by introducing an abstract connection interface, Bluetooth implementation, and centralizing common communication types.
2026-02-06 fix: Correct keyboard button text updates and add new GUI tests for controls, busy view, and main window components.
2026-02-10 feat: Implement Python virtual environment setup and enhance Raspberry Pi detection in the installation script.
2026-02-10 feat: Prevent `install.sh` from running as root and clarify internal `sudo` usage.
2026-02-14 refactor: Clear user messages after user input, adjust board check abort behavior, and enhance the application restart mechanism.
2026-02-14 feat: Mock a connected balance board and streamline the board connection check flow.
2026-02-14 feat: add ABORT command to mockup communication interface
2026-02-14 fix: Set QComboBox view to QListView to resolve Wayland coordinate issues.
2026-02-14 refactor: Remove QApplication attributes for touch event synthesis.
2026-02-14 feat: Add ListSelector and SelectorButton widgets, enabling generic item selection in the GUI.
2026-02-14 feat: Implement a two-column item layout, enhance scroll area interaction with gesture support, and add margins for window positioning.
2026-02-14 test: add integration tests for GUI keyboard, numpad, and list selector input methods.
2026-02-14 style: Remove fixed minimum height for buttons in the list selector.
2026-02-14 fix: Adjust Wayland display rotation and X11/udev touch input calibration matrices.
2026-02-15 refactor: improve install script with modular functions, verbosity control, and enhanced error handling.
2026-02-15 feat: Improve overlay widget touch interaction and event handling, preventing unintended closures and enhancing scrolling.
2026-02-15 fix: Ensure widgets respect maximum size constraints and adjust correctly before positioning.
2026-02-21 refactor: Adjust `QScroller` properties for improved scroll/click distinction and refine event filtering to block events only on the ListSelector itself.
2026-02-28 refactor: Remove debugging logs and event filtering, and refine QScroller properties for improved touchscreen interaction.
2026-02-28 refactor: Remove logging, time-based delays, and specific touchscreen scroll properties from ListSelector.
2026-02-28 feat: Reimplement Bluetooth communication using native sockets and remove PyBluez dependency.
2026-02-28 refactor: replace `is_busy` property with `can_start_order` and `can_access_admin` for improved state management.
2026-02-28 fix: Add explicit None check for amount before processing single ingredient action.
2026-02-28 feat: Move MAC address reset functionality from settings to the shared system view.
2026-02-28 Refactor: bluetooth `read_line` now returns `None` instead of an error `RawResponse` on communication failures.
2026-02-28 feat: Improve Bluetooth device discovery with scanning and add automatic pairing on connection failure.
2026-03-07 fix: Typo in filename
2026-03-30 docs: add project structure documentation and overhaul main README with updated installation and feature guides
